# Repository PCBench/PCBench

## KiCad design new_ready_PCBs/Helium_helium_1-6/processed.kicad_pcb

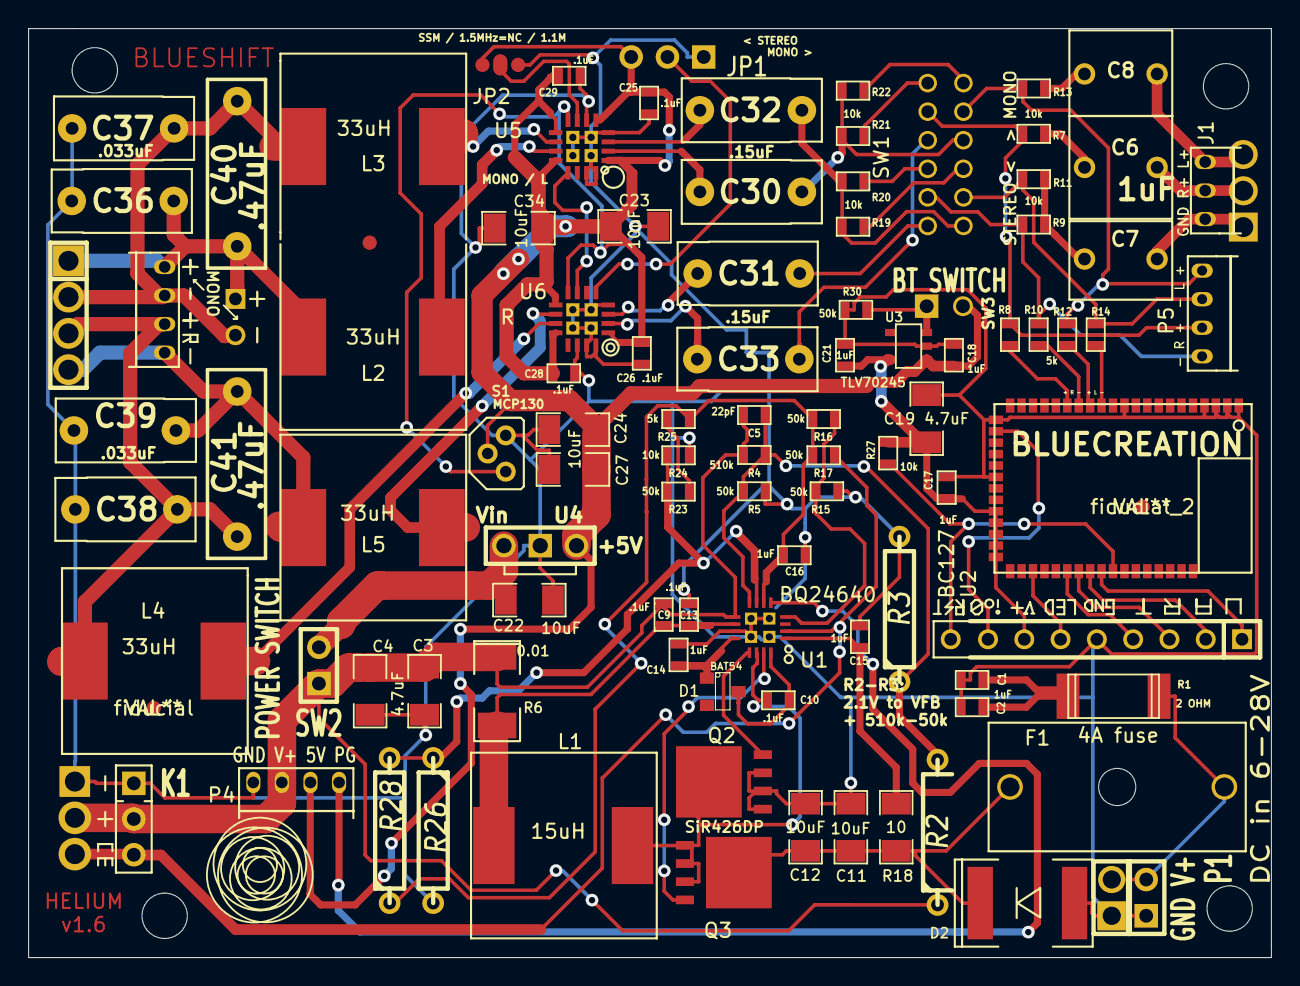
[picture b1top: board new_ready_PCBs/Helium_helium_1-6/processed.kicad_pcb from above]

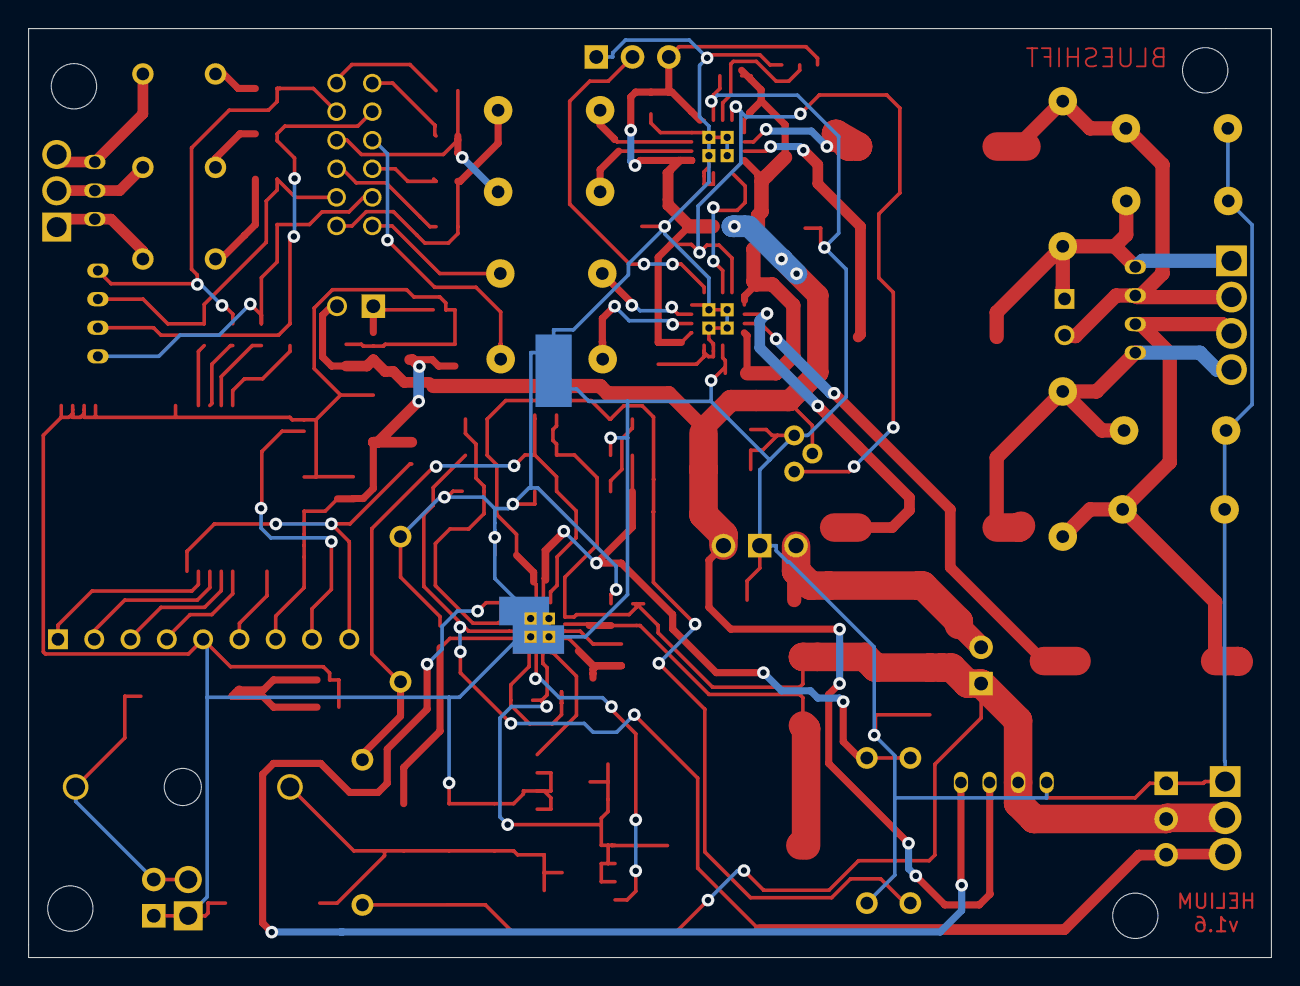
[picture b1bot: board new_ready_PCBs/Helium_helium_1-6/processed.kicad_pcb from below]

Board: 2 copper layers, 87.0 x 65.0 mm, 112 parts (2 on the bottom side), 69 nets.

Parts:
C1, C2, C14, C15, C16, C17, C18, C21: 1uF; SM0603
C3, C4, C19: 4.7uF; SM1206
C5: 22pF; SM0603
C6, C7, C8: 1uF; cnp_7mm_035holes
C9, C10, C13, C25, C26, C28, C29: .1uF; SM0603
C11, C12, C22, C23, C24, C27, C34: 10uF; SM1206
C30, C31, C32, C33: .15uF; cnp_10x4.5mm
C36, C37, C38, C39: .033uF; cnp_10x4.5mm
C40, C41: .47uF; cnp_13x4mm
D1: BAT54; SOT23
D2: 10A diode; SM2010
F1: 4A fuse; fuse
J1: GND R+ L+; h3_2mm
JP1: < STEREO; SIL-3
JP2: SSM / 1.5MHz=NC / 1.1M; jump
K1: TO SUPERCAPS: GND / V+ / CE; SIL-4
L1: 15uH; SRR1280 inductor
L2: 33uH; SRR1280_ind_outline
L3, L4, L5: 33uH; SRR1280 inductor
P1: GND V+; SIL-2
P2: 4xUART/GND/LED/V+/IO; SIL-8-outputs
P3, P5: CONN_4; h4_2mm
P4: GND V+ 5V PG; h4_2mm
Q2, Q3: SiR426DP; PowerPak SO-8 Single
R1: 2 OHM; r_2512
R2: 931k MONO ONLY; R4
R3, R26, R28: DNP; R4
R4: 510k; SM0603
R5, R15, R16, R17, R23, R30: 50k; SM0603
R6: 0.01; SM2010
R7, R9, R11, R13, R19, R20, R21, R22, R24, R27: 10k; SM0603
R8, R10, R12, R14, R25: 5k; SM0603
R18: 10; SM1206
S1: MCP130; TO92PN
SIL-2, SIL-2_2: Val**; SIL-2
SIL-3, SIL-3_2: Val**; SIL-3
SIL-4: Val**; SIL-4
SW1: STEREO < > MONO; 4PDT MMS42R
SW2: POWER SWITCH; SIL-2
SW3: BT SWITCH; SIL-2
U1: BQ24640; BQ24640 QFN16
U2: BC127; bC127
U3: TLV70245; SOT23-5
U4: U4; SIL-3
U5: MONO / L; max9759
U6: R; max9759
XXX1, XXX3: SHORT!
fiducial: VAL**; fiducial
fiducial_2, fiducial_3: VAL**; fiducial
hole: Val**; hole
hole_2, hole_3, hole_4: Val**; hole
xxx2: short; SHORT!

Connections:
CAPGND: C1.2, C2.2, C3.2, C4.2, C11.2, C12.2, C14.2, C17.2, C18.2, C19.2, C21.2, C22.2, C24.2, C27.2, C28.2, C29.2, C34.2, C36.2, C37.1, C38.2, C39.1, D2.1, K1.1, P1.2, P2.5, P4.1, Q2.1, Q2.2, Q2.3, R24.2, R26.2, R30.2, S1.3, SIL-2.2, SIL-3_2.1, U1.11, U2.1, U2.2, U2.3, U2.4, U2.11, U2.22, U2.27, U3.2, U4.2, U5.6, U6.14, XXX1.2, xxx2.1
CAPV+: C3.1, C4.1, C5.1, C9.2, K1.2, P4.2, R2.1, R4.1, R6.1, SIL-3_2.2, SW2.1, U1.9
CE: K1.3, R17.2, SIL-3_2.3, U1.2
GNDA: C13.2, C15.2, C16.2, C23.2, C25.2, C26.2, JP1.1, JP2.3, R3.2, R5.2, R15.2, U5.4, U5.15, U5.16, U6.4, U6.15, U6.16, XXX1.1, xxx2.2
unnamed: JP1.2, U6.5
unnamed: P2.1, U2.43
unnamed: R22.1, SW1.12
unnamed: P5.1, R9.2, R10.1, SW1.2
unnamed: P5.2, R7.2, R8.1, SW1.5
unnamed: R21.1, SW1.6
unnamed: P5.3, R11.2, R14.1, SW1.8
unnamed: R20.1, SW1.3
unnamed: R19.1, SW1.9
unnamed: R10.2, U2.15
unnamed: P2.2, U2.42
unnamed: P2.3, U2.41
unnamed: P2.4, U2.40
unnamed: P2.9, R27.1, U2.44
unnamed: R14.2, U2.13
unnamed: C6.1, J1.2, SIL-3.2
unnamed: R12.2, U2.14
unnamed: R8.2, U2.16
unnamed: P5.4, R12.1, R13.2, SW1.11
unnamed: C30.1, U5.2
unnamed: C32.1, U5.3
unnamed: C31.2, U6.3
unnamed: C33.2, U6.2
unnamed: C5.2, R2.2, R3.1, R4.2, R5.1, U1.8
unnamed: C10.2, D1.2, U1.16
unnamed: C14.1, D1.1, U1.12
unnamed: R15.1, R16.2, U1.4
unnamed: L2.1, U5.11
unnamed: L5.1, U6.10
unnamed: L4.1, U6.11
unnamed: U5.13, U6.7
unnamed: C22.1, SW2.2, U4.3
unnamed: C8.1, J1.3, SIL-3.3
unnamed: R23.1, R25.2
unnamed: R23.2, R24.1, R26.1, R28.2, U1.7
unnamed: C31.1, SW1.1
unnamed: F1.1, P1.1, R1.1, SIL-2.1
unnamed: P4.4, U1.5
unnamed: C7.2, R9.1, R11.1
unnamed: C7.1, J1.1, SIL-3.1
unnamed: C8.2, R13.1
unnamed: L3.1, U5.10
unnamed: C32.2, R19.2, R20.2, SW1.7
unnamed: C30.2, R21.2, R22.2, SW1.10
unnamed: C33.1, SW1.4
unnamed: C6.2, R7.1
unnamed: P2.6, U2.37
unnamed: P2.8, U2.23
unnamed: JP2.2, U5.7
unnamed: C23.1, C25.1, C26.1, JP1.3, JP2.1, S1.1, U5.1, U5.5, U5.8, U6.1, U6.8, XXX3.2
unnamed: C11.1, C12.1, D2.2, F1.2, Q3.5, Q3.6, Q3.7, Q3.8, R18.1
unnamed: C10.1, L1.1, Q2.5, Q2.6, Q2.7, Q2.8, Q3.1, Q3.2, Q3.3, U1.14
unnamed: Q3.4, U1.15
unnamed: C16.1, R16.1, R17.1, R25.1, R28.1, U1.6
unnamed: Q2.4, U1.13
unnamed: C1.1, C2.1, R1.2
unnamed: C15.1, R18.2, U1.1
unnamed: C18.1, C24.1, C27.1, C28.1, C29.1, C34.1, P4.3, S1.2, SW3.2, U3.1, U4.1, U5.9, U5.12, U6.9, U6.12, XXX3.1
unnamed: C36.1, C40.1, L2.2, P3.1, SIL-2_2.1, SIL-4.1
unnamed: C37.2, C40.2, L3.2, P3.2, SIL-2_2.2, SIL-4.2
unnamed: C9.1, C13.1, L1.2, R6.2, U1.10
unnamed: R30.1, SW3.1, U3.3
unnamed: C17.1, C19.1, C21.1, P2.7, R27.2, U2.30, U2.31, U2.32, U2.33, U2.34, U3.5
unnamed: C38.1, C41.1, L4.2, P3.3, SIL-4.3
unnamed: C39.2, C41.2, L5.2, P3.4, SIL-4.4

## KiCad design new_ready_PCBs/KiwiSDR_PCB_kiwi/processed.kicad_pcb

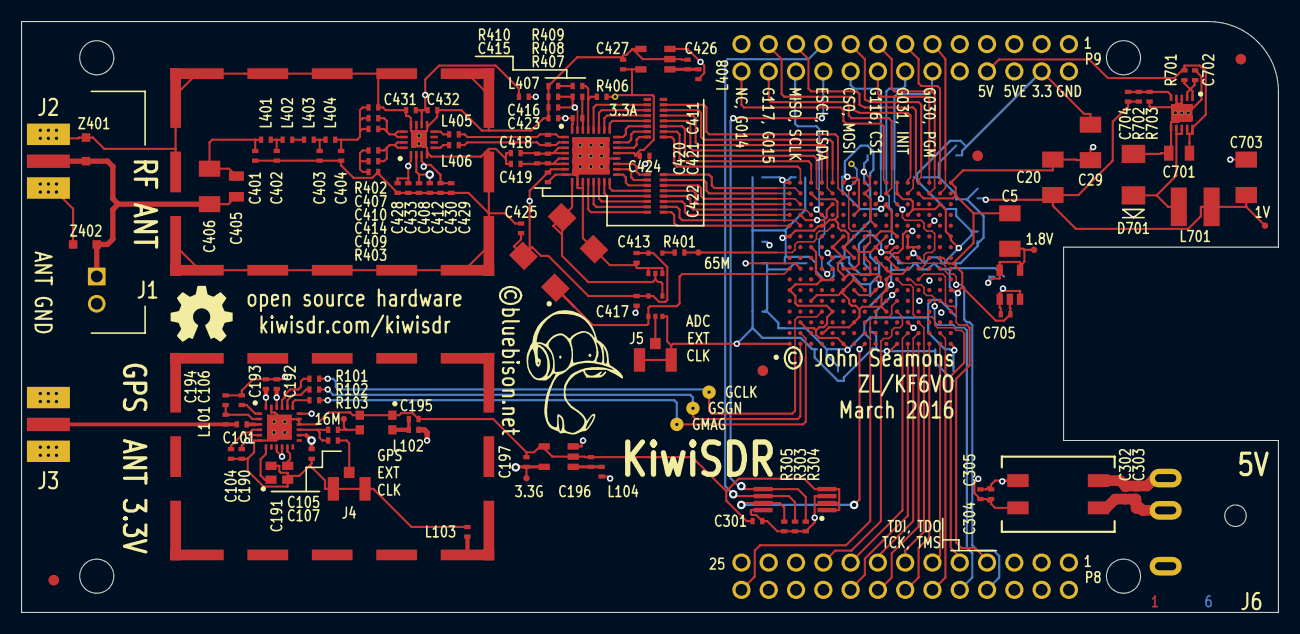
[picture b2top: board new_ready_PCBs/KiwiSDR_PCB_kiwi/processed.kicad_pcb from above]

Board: 6 copper layers, 117.0 x 55.0 mm, 173 parts (0 on the bottom side), 119 nets.

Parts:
C1, C2, C3, C6, C7, C8, C11, C12, C13, C15, C16, C23, C24, C25, C26, C30, C31, C32, C33, C36, C37, C38, C39, C42, C302, C304, C410, C414: 470n; kiwi-SM0402
C5, C20, C29, C703: 100u; kiwi-SM1206
C9, C14, C17, C18, C27, C28, C34, C35, C40, C41, C706: 4.7u; kiwi-SM0402
C101, C104: 22p; kiwi-SM0402
C105, C106, C193, C303, C305, C413, C417, C425: 10n; kiwi-SM0402
C107: DNL 10n; kiwi-SM0402
C190, C191, C192, C195, C301, C421, C422, C423, C424, C429, C431, C433, C702, C704: 100n; kiwi-SM0402
C194, C408, C411, C416: 100p; kiwi-SM0402
C196, C197, C418, C419, C426, C427, C705: 1u; kiwi-SM0402
C401, C404: 56p/100; kiwi-SM0402
C402, C403: 160p/50; kiwi-SM0402
C405: 1n/100; kiwi-SM0805
C406: 470n/100; kiwi-SM1206
C407, C409, C428, C430, C432: 1n; kiwi-SM0402
C412, C415, C420: 2.2u; kiwi-SM0402
C701: 22u; kiwi-SM0805
D701: SR 5A 40V; kiwi-DO214_AA
FID1, FID2: FPGA FIDUCIAL; kiwi-FIDUCIAL
FID3, FID4, FID5, FID6: GLOBAL FIDUCIAL; kiwi-FIDUCIAL
FL101: SAW L1; kiwi-SAW
GFX1: LOGO; kiwi-KIWI_10MM
GFX2: OSHW; kiwi-OSHW_6MM
J1: TB_2; kiwi-TB_2P_2_54MM
J2, J3: SMA; kiwi-SMA_OPL_EM
J4, J5: DNL U.FL; kiwi-U.FL
J6: POWER JACK 2.1MM; kiwi-JACK_2_1MM_TH
L101: 39nH; kiwi-SM0402
L102, L103, L104, L407, L408: FB 600Z; kiwi-SM0402
L401, L404: 330nH; kiwi-SM0402
L402: 270nH; kiwi-SM0402
L403, L405, L406: 150nH; kiwi-SM0402
L701: 1uH 3.7A; kiwi-INDUCTOR_4x4
R101, R102, R103, R401: 100R; kiwi-SM0402
R303, R304, R305: 5K6; kiwi-SM0402
R402: 66R5; kiwi-SM0402
R403: 28R7; kiwi-SM0402
R404, R405: 100R; kiwi-RNET_CAY16_J8
R406, R409, R410, R703: 10K; kiwi-SM0402
R407: DNL; kiwi-SM0402
R408: 0R; kiwi-SM0402
R701: 10R; kiwi-SM0402
R702: 6K65; kiwi-SM0402
T301: CMC 500uH 1A; kiwi-CMC
TP101, TP105, TP401, TP701, TP702: TEST_POINT; kiwi-TP_600
TP102, TP103, TP104: TEST_POINT; kiwi-TP_VIA_1250
TP301, TP402: TEST_POINT; kiwi-TP_VIA_600
U1: Artix-7 A35; kiwi-FTG256
U101: SE4150L; kiwi-QFN24
U104, U404: LP5907 3.3V 250mA; kiwi-SOT23_5
U301: EEPROM 32Kx8; kiwi-TSSOP8
U401: LTC2248; kiwi-QFN32
U402: 66.6666 MHz; kiwi-XO
U403, U406: NC7SZ125; kiwi-SC70_5
U405: LTC6401-20; kiwi-QFN16
U701: LMR10530Y 1.0V 3A; kiwi-WSON10
U702: LP5907 1.8V 250mA; kiwi-SOT23_5
X101: 16.368 MHz; kiwi-TCXO
Z401, Z402: TVS 3.3V; kiwi-SOD323
ZB1: HEADER 13x2; kiwi-BEAGLEBONE_BLACK
ZR101: RF_SHIELD 29x19; kiwi-RF_SHIELD_29x19_16P
ZR102, ZR402: RF_SHIELD_COVER 29x19; kiwi-RF_SHIELD_COVER
ZR401: RF_SHIELD 29x19; kiwi-RF_SHIELD_29x19

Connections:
1.0: C2.1, C3.1, C8.1, C9.1, C14.1, C15.2, C20.1, C42.2, C703.1, C704.1, L701.2, R702.1, TP701.1, U1.E10, U1.F7, U1.F9, U1.F11, U1.G6, U1.H9, U1.J6, U1.K9, U1.L8
1.8: C1.1, C5.1, C7.1, C13.1, C706.1, TP702.1, U1.F8, U1.G8, U1.G10, U1.J10, U1.K11, U1.L10, U702.4, U702.5
3.3: C6.1, C11.1, C12.1, C16.1, C17.1, C18.1, C23.1, C24.1, C25.1, C26.1, C27.1, C28.1, C29.1, C30.1, C31.1, C32.1, C33.1, C34.1, C35.1, C36.1, C37.1, C38.1, C39.1, C40.1, C41.1, C301.2, R303.1, R304.1, R305.1, U1.A6, U1.A16, U1.B3, U1.B13, U1.C10, U1.D7, U1.E4, U1.E7, U1.E14, U1.F1, U1.H15, U1.J12, U1.L6, U1.L15, U1.L16, U1.M3, U1.M9, U1.M10, U1.M11, U1.M13, U1.N10, U1.P7, U1.R4, U1.R14, U1.T1, U1.T11, U301.3, U301.8, ZB1.903, ZB1.904
3.3A: C413.1, C417.1, C422.2, C423.2, C424.1, C425.1, C427.1, L407.1, R406.1, R407.1, TP402.1, U401.7, U401.21, U401.32, U402.4, U403.5, U404.5, U406.5
3.3G: C190.1, C191.1, C192.2, C193.2, C197.1, L102.2, TP105.1, U101.5, U101.9, U101.10, U101.14, U101.18, U101.22, U101.24, U104.5
5EXT: C304.1, C305.1, T301.1, ZB1.905, ZB1.906
5V: C701.1, C705.1, L104.2, L408.2, R701.1, U104.3, U404.3, U701.9, U701.10, U702.1, U702.3, ZB1.907, ZB1.908
/ADC/AD0: R405.15, U401.12
/ADC/AD1: R405.13, U401.13
/ADC/AD2: R405.11, U401.14
/ADC/AD3: R405.9, U401.15
/ADC/AD4: R405.7, U401.16
/ADC/AD5: R405.5, U401.17
/ADC/AD6: R405.3, U401.18
/ADC/AD7: R405.1, U401.19
/ADC/AD8: R404.15, U401.22
/ADC/AD9: R404.13, U401.23
/ADC/AD10: R404.11, U401.24
/ADC/AD11: R404.9, U401.25
/ADC/AD12: R404.7, U401.26
/ADC/AD13: R404.5, U401.27
/ADC/ADOV: R404.3, U401.28
/ADC/AIN+: C411.1, L405.2, U401.1
/ADC/AIN-: C411.2, L406.2, U401.2
/ADC/ANT+: C405.1, C406.1, J1.1, J2.1, Z401.2, Z402.2
/ADC/AXO: U401.9, U402.3, U403.4, U406.2
/ADC/ECLK: J5.1, U403.2
/ADC/IN+: C407.2, C410.2, U405.13, U405.14
/ADC/IN-: C409.2, C414.2, U405.15, U405.16
/ADC/LCLK: R401.1, U406.4
/ADC/LP1: C401.1, C405.2, C406.2, L401.1
/ADC/LP2: C402.1, L401.2, L402.1
/ADC/LP3: L402.2, L403.1
/ADC/LP4: C403.1, L403.2, L404.1
/ADC/MD1: R409.2, R410.1
/ADC/MODE: R406.2, R409.1, U401.29
/ADC/OUT+: L405.1, U405.8
/ADC/OUT-: L406.1, U405.5
/ADC/REFH: C418.2, C420.1, C421.1, U401.3, U401.4
/ADC/REFL: C419.2, C420.2, C421.2, U401.5, U401.6
/ADC/RF+: C404.1, C407.1, C410.1, L404.2, R402.1
/ADC/RF-: C409.1, C414.1, R403.2
/ADC/SENSE: R407.2, R408.2, U401.30
/ADC/VA: C428.2, C429.2, C430.2, C431.1, C432.1, C433.2, L407.2, U405.1, U405.3, U405.10
/ADC/VCM: C408.1, C412.1, C415.1, C416.1, R408.1, U401.31, U405.2
/ADC/VIN: C426.1, L408.1, U404.1
/BeagleBone/5V_NEG: C302.2, C303.2, J6.2, J6.3, T301.3
/BeagleBone/5V_POS: C302.1, C303.1, J6.1, T301.4
/BeagleBone/CS0: U1.N16, ZB1.917
/BeagleBone/CS1: U1.P16, ZB1.916
/BeagleBone/DONE: TP301.1, U1.H10
/BeagleBone/ESCL: R303.2, U301.6, ZB1.919
/BeagleBone/ESDA: R304.2, U301.5, ZB1.920
/BeagleBone/G014: U1.K16, ZB1.926
/BeagleBone/G015: U1.K15, ZB1.924
/BeagleBone/G030: U1.R15, ZB1.911
/BeagleBone/G031: U1.R16, ZB1.913
/BeagleBone/G116: U1.P15, ZB1.915
/BeagleBone/G117: U1.M16, ZB1.923
/BeagleBone/INIT: U1.K10, ZB1.914
/BeagleBone/MISO: U1.M15, ZB1.921
/BeagleBone/MOSI: U1.J14, ZB1.918
/BeagleBone/PGM: U1.L9, ZB1.912
/BeagleBone/TCK: U1.L7, ZB1.809
/BeagleBone/TDI: U1.N7, ZB1.807
/BeagleBone/TDO: U1.N8, ZB1.808
/BeagleBone/TMS: U1.M7, ZB1.810
/GPS/EOSC: C107.2, J4.1
/GPS/GBIAS: C194.2, L101.2, U101.2
/GPS/GPS: C101.1, J3.1, L101.1
/GPS/GPS2: C101.2, U101.3
/GPS/LCLK: R101.1, U101.21
/GPS/LMAG: R103.1, U101.19
/GPS/LNA: C104.1, U101.4
/GPS/LSGN: R102.1, U101.20
/GPS/RING: L103.2, ZR101.1
/GPS/SAW1: FL101.1, U101.7
/GPS/SAW2: FL101.3, U101.11
/GPS/TCXO1: C105.1, C107.1, U101.15
/GPS/TCXO2: C105.2, TP101.1, X101.3
/GPS/TXOP: C195.1, L102.1, X101.4
/GPS/VAGC: C106.2, U101.1
/GPS/VIN: C196.1, L104.1, U104.1
/Power_Supplies/EN: C702.1, R701.2, U701.1, U701.2
/Power_Supplies/FB: C704.2, R702.2, R703.1, U701.5
/Power_Supplies/SW1: D701.1, L701.1, U701.7, U701.8
ACLK: R401.2, TP401.1, U1.E12
AEXT: U1.A8, U402.1, U403.1
D0: R405.16, U1.A12
D1: R405.14, U1.B12
D2: R405.12, U1.A13
D3: R405.10, U1.C13
D4: R405.8, U1.A14
D5: R405.6, U1.B14
D6: R405.4, U1.A15
D7: R405.2, U1.B15
D8: R404.16, U1.B16
D9: R404.14, U1.C16
D10: R404.12, U1.D15
D11: R404.10, U1.D16
D12: R404.8, U1.E15
D13: R404.6, U1.E16
EWP: R305.2, U1.H1, U301.7
G022: U1.L4, ZB1.819
G023: U1.N3, ZB1.813
G026: U1.P1, ZB1.814
G027: U1.M2, ZB1.817
G112: U1.R2, ZB1.812
G113: U1.R1, ZB1.811
G114: U1.N1, ZB1.816
G115: U1.N2, ZB1.815
G129: U1.L5, ZB1.826
G201: U1.M1, ZB1.818
GCLK: R101.2, TP102.1, U1.D4
GMAG: R103.2, TP104.1, U1.B2
GND: C1.2, C2.2, C3.2, C5.2, C6.2, C7.2, C8.2, C9.2, C11.2, C12.2, C13.2, C14.2, C15.1, C16.2, C17.2, C18.2, C20.2, C23.2, C24.2, C25.2, C26.2, C27.2, C28.2, C29.2, C30.2, C31.2, C32.2, C33.2, C34.2, C35.2, C36.2, C37.2, C38.2, C39.2, C40.2, C41.2, C42.1, C104.2, C106.1, C190.2, C191.2, C192.1, C193.1, C194.1, C195.2, C196.2, C197.2, C301.1, C304.2, C305.2, C401.2, C402.2, C403.2, C404.2, C408.2, C412.2, C413.2, C415.2, C416.2, C417.2, C418.1, C419.1, C422.1, C423.1, C424.2, C425.2, C426.2, C427.2, C428.1, C429.1, C430.1, C431.2, C432.2, C433.1, C701.2, C702.2, C703.2, C705.2, C706.2, D701.2, FL101.2, FL101.4, J1.2, J2.2, J2.3, J3.2, J3.3, J4.2, J4.3, J5.2, J5.3, L103.1, R402.2, R403.1, R410.2, R703.2, T301.2, U1.A1, U1.A11, U1.B8, U1.C5, U1.C15, U1.D2, U1.D12, U1.E9, U1.F6, U1.F10, U1.F16, U1.G3, U1.G7, U1.G9, U1.G13, U1.H6, U1.J9, U1.J11, U1.K4, U1.K6, U1.K7, U1.K8, U1.K14, U1.L1, U1.L11, U1.M8, U1.N5, U1.N15, U1.P12, U1.R9, U1.T6, U1.T16, U101.6, U101.16, U101.17, U101.23, U101.PAD, U104.2, U104.4, U301.1, U301.2, U301.4, U401.8, U401.10, U401.11, U401.20, U401.PAD, U402.2, U403.3, U404.2, U404.4, U405.4, U405.9, U405.11, U405.12, U405.PAD, U406.1, U406.3, U701.3, U701.4, U701.6, U701.PAD, U702.2, X101.1, X101.2, Z401.1, Z402.1, ZB1.901, ZB1.902, ZR401.0
GSGN: R102.2, TP103.1, U1.B1
OVFL: R404.4, U1.F15
SCLK: U1.D13, U1.E8, ZB1.922

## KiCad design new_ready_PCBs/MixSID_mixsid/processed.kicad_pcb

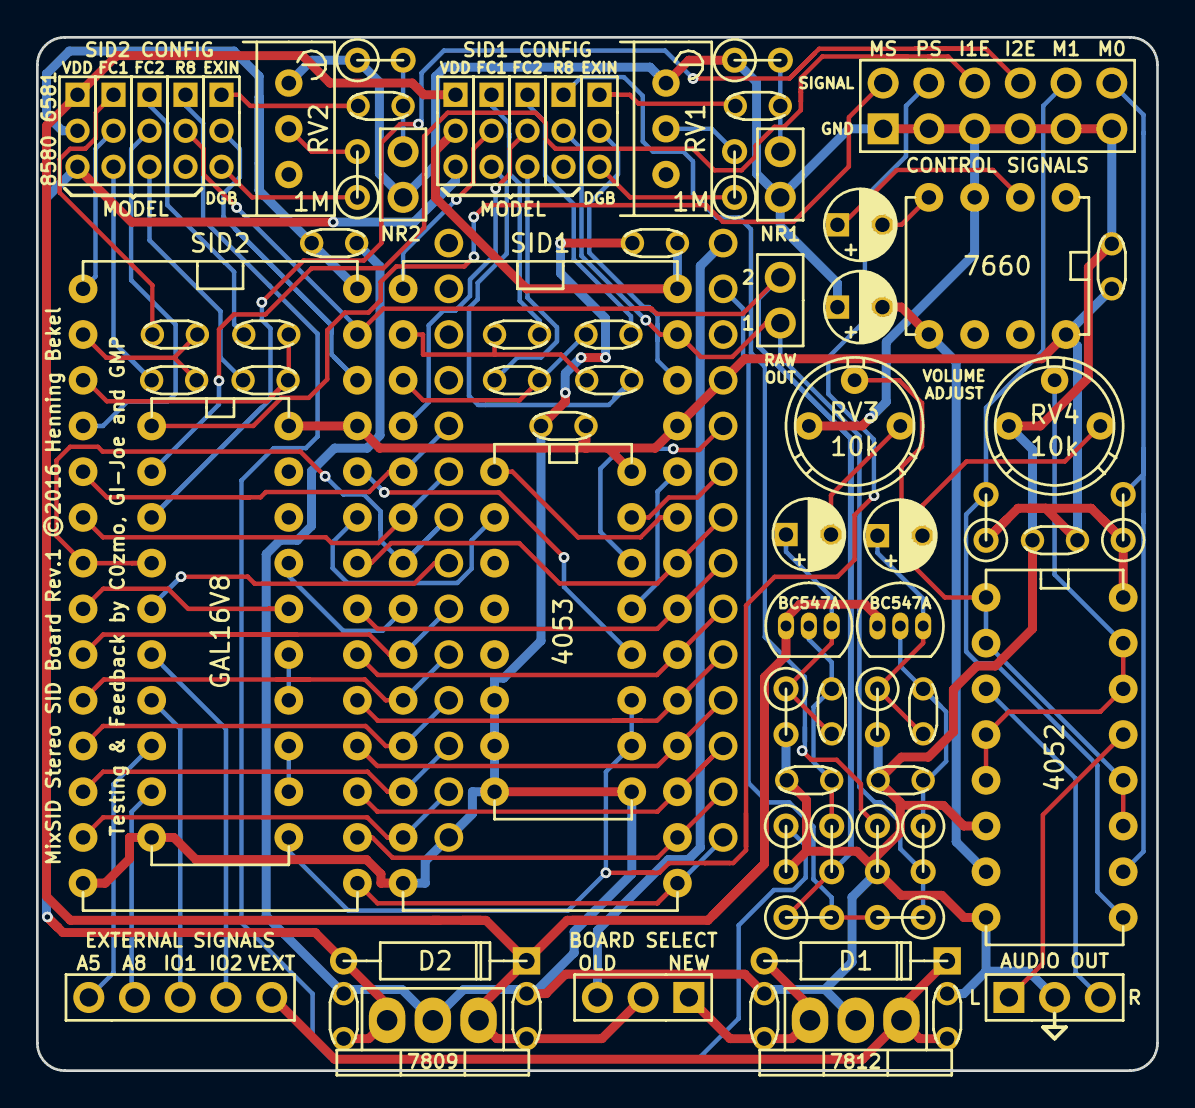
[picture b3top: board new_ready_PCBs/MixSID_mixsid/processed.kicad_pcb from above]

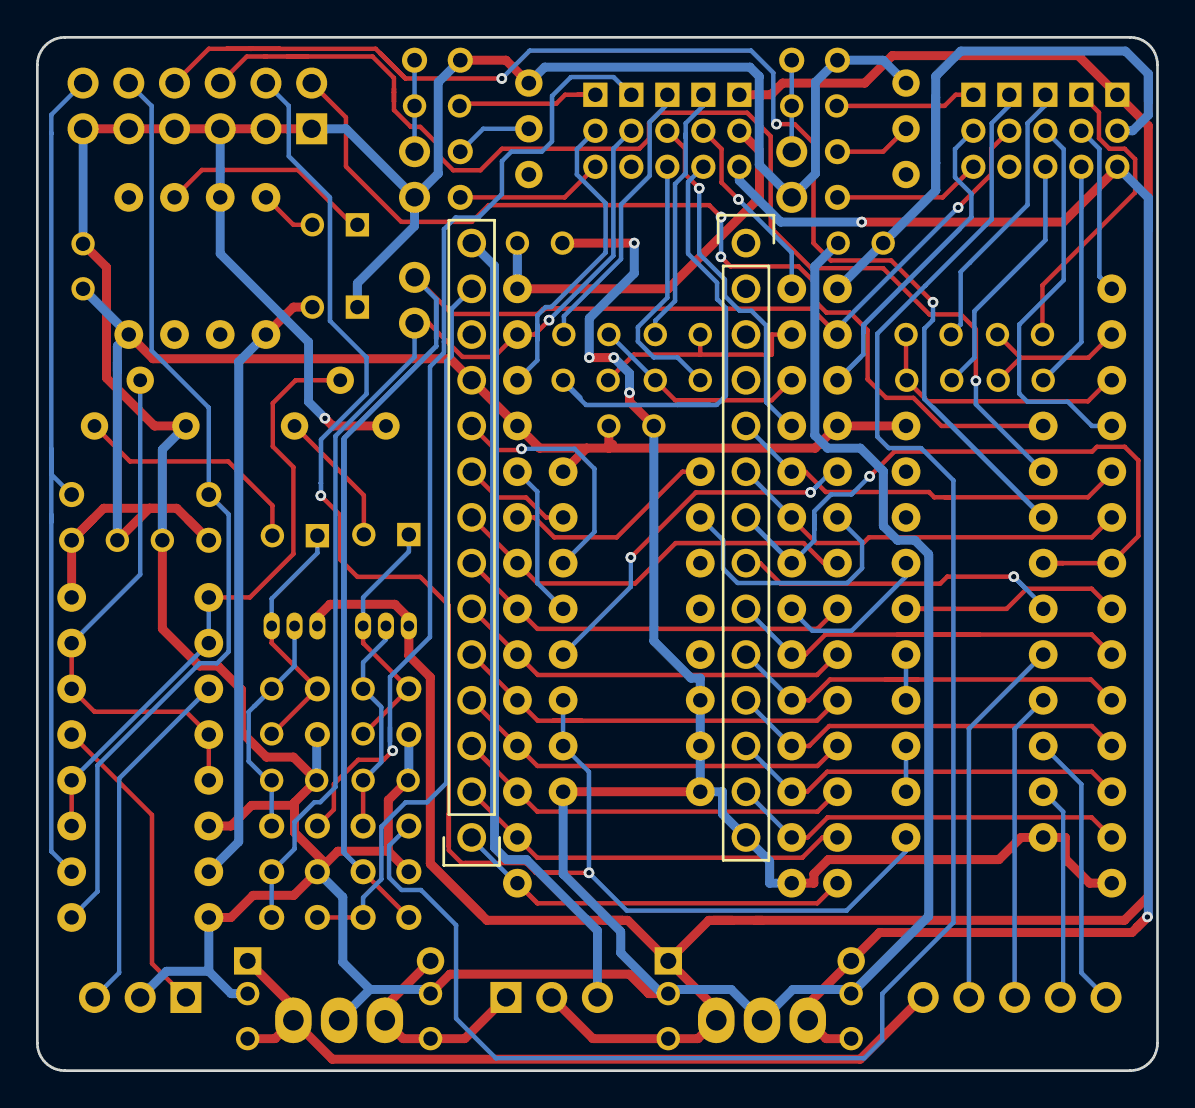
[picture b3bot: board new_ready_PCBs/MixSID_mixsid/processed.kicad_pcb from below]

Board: 2 copper layers, 62.2 x 57.4 mm, 76 parts (2 on the bottom side), 90 nets.

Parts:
C1, C3, C5, C7, C9, C11, C16, C21: 470p; C_Disc_D3_P2.5
C2, C4, C10, C12: 22n; C_Disc_D3_P2.5
C6, C8, C13, C14, C23, C24, C25, C26, C27: 100n; C_Disc_D3_P2.5
C15, C20: 1n; C_Disc_D3_P2.5
C17, C18: 10u; C_Radial_D5_L6_P2.5
C19, C22: 10uF; C_Radial_D5_L6_P2.5
D1, D2: 1N4002; DO-41
JP1: SUPPLY2; Pin_Header_Straight_1x03_Pitch2.00mm_Jumper_1-2
JP2: S2CAP2; Pin_Header_Straight_1x03_Pitch2.00mm_Jumper_1-2
JP3: S2CAP1; Pin_Header_Straight_1x03_Pitch2.00mm
JP4: BOARD; Pin_Header_Straight_1x03
JP5: SUPPLY1; Pin_Header_Straight_1x03_Pitch2.00mm_Jumper_2-3
JP6: S1CAP2; Pin_Header_Straight_1x03_Pitch2.00mm_Jumper_2-3
JP7: S1CAP1; Pin_Header_Straight_1x03_Pitch2.00mm_Jumper_2-3
JP8: INPUT2; Pin_Header_Straight_1x03_Pitch2.00mm_Jumper_1-2
JP9: NR1; Pin_Header_Straight_1x02
JP10: NR2; Pin_Header_Straight_1x02
JP11: INPUT1; Pin_Header_Straight_1x03_Pitch2.00mm_Jumper_2-3
JP12: J2R8; Pin_Header_Straight_1x03_Pitch2.00mm_Jumper_1-2
JP13: J1R8; Pin_Header_Straight_1x03_Pitch2.00mm_Jumper_2-3
P1: INPUT; Pin_Header_Straight_1x05
P2: CONTROL; Pin_Header_Straight_2x06
P3: RAW; Pin_Header_Straight_1x02
P4: SOCKET LEFT; Pin_Header_Straight_1x14
P5: OUTPUT; Pin_Header_Straight_1x03
P6: SOCKET RIGHT; Pin_Header_Straight_1x14
Q1, Q2: BC547; TO-92_Inline_Narrow_Oval
R1, R10: 220k; R1
R2, R9: 100k; R1
R3, R5, R6, R12, R13, R14: 1k; R1
R4, R11: 10k; R1
R7, R8: 4k7; R1
RV1, RV2: 1M; Potentiometer_Bourns_3296W_3-8Zoll_Inline_ScrewUp
RV3, RV4: 10k; Potentiometer_Bourns_3339P_Angular_ScrewUp
U1: GAL16V8; DIP-20_W7.62mm
U2: SID2; DIP-28_W15.24mm
U3: 7812; TO-220
U4: 7809; TO-220
U5: SID1; DIP-28_W15.24mm
U6: 4052; DIP-16_W7.62mm
U7: 4053; DIP-16_W7.62mm
U8: 7660; DIP-8_W7.62mm

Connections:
/+9V: C8.1, D2.2, JP1.3, JP5.3, U4.3
/+12V: C7.1, D2.1, JP1.1, JP4.2, JP5.1, Q1.1, Q2.1, U4.1
/A0: P4.9, U2.9, U5.9
/A1: P4.10, U2.10, U5.10
/A2: P4.11, U2.11, U5.11
/A3: P4.12, U2.12, U5.12
/A4: P4.13, U2.13, U5.13
/A5: P1.1, U1.8
/A8: P1.2, U1.9
/CLK: P4.6, U2.6, U5.6
/D0: P6.1, U2.15, U5.15
/D1: P6.2, U2.16, U5.16
/D2: P6.3, U2.17, U5.17
/D3: P6.4, U2.18, U5.18
/D4: P6.5, U2.19, U5.19
/D5: P6.6, U2.20, U5.20
/D6: P6.7, U2.21, U5.21
/D7: P6.8, U2.22, U5.22
/LEFT: RV3.2, U6.1, U6.2, U6.11, U6.12
/LEFT_OUT: P5.1, U6.13
/M0: P2.12, R7.2, U6.10
/M1: P2.10, R8.2, U6.9
/MONO_OUT: P6.13, R13.2, R14.2
/MS: P2.2, U1.1
/POTX: P6.10, U7.14
/POTX1: U5.24, U7.13
/POTX2: U2.24, U7.12
/POTY: P6.9, U7.15
/POTY1: U5.23, U7.1
/POTY2: U2.23, U7.2
/PS: P2.4, U1.11, U7.10, U7.11
/PWR: C6.1, D1.2, JP4.1, U3.3
/PWR1: C27.1, JP5.2, U5.28
/PWR2: C26.1, JP1.2, U2.28
/RIGHT: RV4.2, U6.4, U6.5, U6.14, U6.15
/RIGHT_OUT: P5.3, U6.3
/RW: P4.7, U1.4, U2.7, U5.7
/S1IN: JP11.2, U5.26
/S1OUT: JP13.2, P3.2, R11.2, R14.1, U5.27
/S2IN: JP8.2, U2.26
/S2OUT: JP12.2, P3.1, R4.2, R13.1, U2.27
/VEE: C18.2, U6.7, U8.5
/VEXT: C5.1, D1.1, P1.5, U3.1
/~CS: P4.8, U1.5
/~CS1: U1.17, U5.8
/~CS2: U1.16, U2.8
/~IO1: P1.3, U1.7
/~IO1EN: P2.6, U1.2
/~IO2: P1.4, U1.6
/~IO2EN: P2.8, U1.3
/~RES: P4.5, U2.5, U5.5
GND: C5.2, C6.2, C7.2, C8.2, C15.2, C18.1, C20.2, C23.2, C24.2, C25.2, C26.2, C27.2, JP9.2, JP10.2, P2.1, P2.3, P2.5, P2.7, P2.9, P2.11, P4.14, P5.2, R2.1, R3.2, R5.2, R6.2, R9.1, R12.2, RV1.1, RV2.1, RV3.1, RV4.1, U1.10, U2.14, U3.2, U4.2, U5.14, U6.6, U6.8, U7.6, U7.7, U7.8, U7.9, U8.3
unnamed: C1.1, C2.2, U2.3
unnamed: C1.2, JP2.1
unnamed: C2.1, JP2.3
unnamed: C3.1, C4.2, U2.2
unnamed: C3.2, JP3.1
unnamed: C4.1, JP3.3
unnamed: C9.2, JP6.1
unnamed: C10.1, JP6.3
unnamed: C9.1, C10.2, U5.3
unnamed: C11.1, C12.2, U5.2
unnamed: C11.2, JP7.1
unnamed: C12.1, JP7.3
unnamed: C13.1, JP10.1, R9.2
unnamed: C13.2, JP8.1
unnamed: C14.1, JP9.1, R2.2
unnamed: C14.2, JP11.1
unnamed: C15.1, C16.1, Q1.2, R4.1
unnamed: C16.2, C19.1, Q1.3, R5.1
unnamed: C17.1, U8.2
unnamed: C17.2, U8.4
unnamed: C19.2, RV3.3
unnamed: C20.1, C21.1, Q2.2, R11.1
unnamed: C21.2, C22.1, Q2.3, R12.1
unnamed: C22.2, RV4.3
unnamed: JP2.2, U2.4
unnamed: JP3.2, U2.1
unnamed: JP6.2, U5.4
unnamed: JP7.2, U5.1
unnamed: JP8.3, R1.1
unnamed: JP11.3, R10.1
unnamed: JP12.1, R3.1
unnamed: JP13.1, R6.1
unnamed: R1.2, RV2.2
unnamed: R10.2, RV1.2
unnamed: U1.12, U1.13
unnamed: U1.14, U1.15
VCC: C23.1, C24.1, C25.1, P6.11, R7.1, R8.1, U1.20, U2.25, U5.25, U6.16, U7.16, U8.8
VDD: JP4.3, P6.14

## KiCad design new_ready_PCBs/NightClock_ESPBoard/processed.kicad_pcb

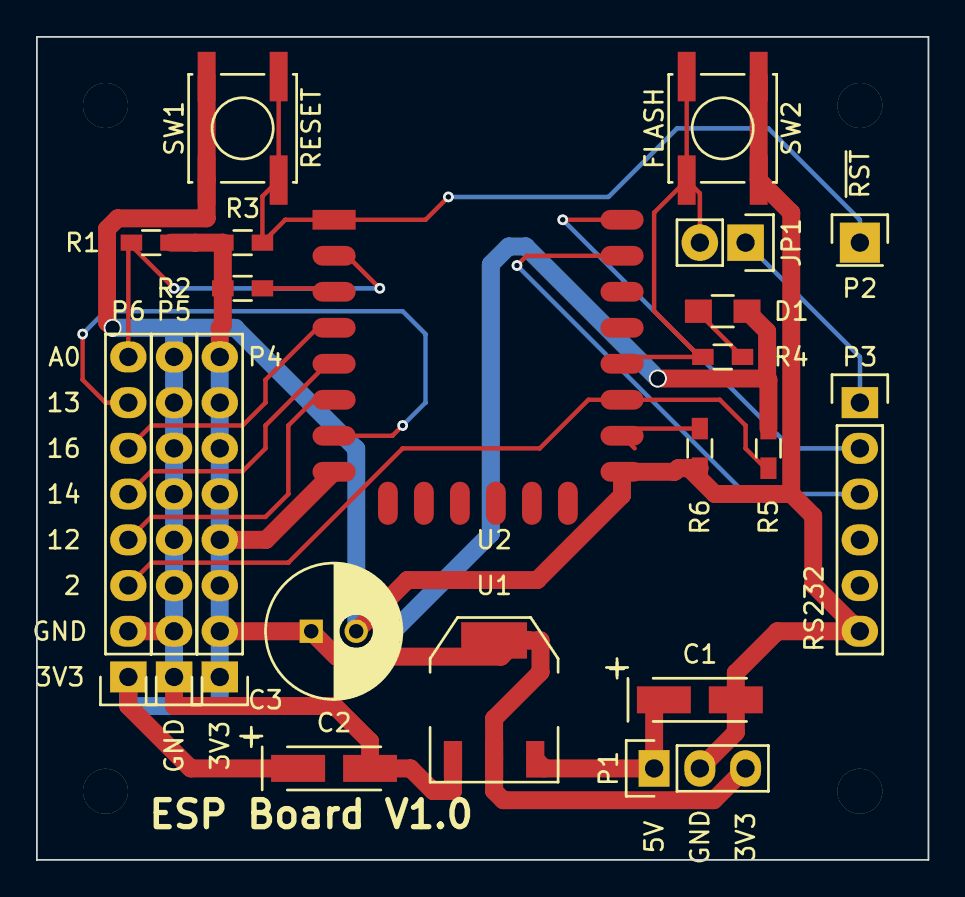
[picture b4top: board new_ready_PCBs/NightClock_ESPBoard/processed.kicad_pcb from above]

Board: 2 copper layers, 49.5 x 45.7 mm, 21 parts (0 on the bottom side), 17 nets.

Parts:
C1, C2: 10u; TantalC_SizeA_EIA-3216_HandSoldering
C3: 1000u; C_Radial_D7.5_L11.2_P2.5
D1: LED; R_0805_HandSoldering
JP1: AUTO_FLASH; Pin_Header_Straight_1x02
P1: PWR; Pin_Header_Straight_1x03
P2: EXT_RESET; Pin_Header_Straight_1x01
P3: RS232; Pin_Header_Straight_1x06
P4: 3.3V; Pin_Header_Straight_1x08
P5: Gnd; Pin_Header_Straight_1x08
P6: GPIO; Pin_Header_Straight_1x08
R1: 470k; R_0603_HandSoldering
R2, R3, R5, R6: 10k; R_0603_HandSoldering
R4: 330R; R_0603_HandSoldering
SW1: RESET; SW_SPST_EVPBF
SW2: FLASH; SW_SPST_EVPBF
U1: LM1117-3.3; SOT-223
U2: ESP-12E

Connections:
+3V3: C2.1, C3.1, D1.2, P1.3, P4.1, P4.2, P4.3, P4.4, P4.5, P4.6, P4.7, P4.8, P6.1, R1.1, R2.1, R3.1, R5.1, U1.2, U1.4, U2.8
+5V: C1.1, P1.1, U1.3
/ESP_ADC: P6.8, R1.2, U2.2
/ESP_CH_PD: R2.2, U2.3
/ESP_GPIO0: JP1.2, R4.2, SW2.2, U2.18
/ESP_GPIO2: P6.3, R5.2, U2.17
/ESP_GPIO12: P6.4, U2.6
/ESP_GPIO13: P6.7, U2.7
/ESP_GPIO14: P6.5, U2.5
/ESP_GPIO15: R6.1, U2.16
/ESP_GPIO16: P6.6, U2.4
/ESP_RESET: P2.1, R3.2, SW1.2, U2.1
/ESP_RX_IN: P3.3, U2.21
/ESP_TX_OUT: P3.2, U2.22
/SERIAL_DTR: JP1.1, P3.1
GNDPWR: C1.2, C2.2, C3.2, P1.2, P3.6, P5.1, P5.2, P5.3, P5.4, P5.5, P5.6, P5.7, P5.8, P6.2, R6.2, SW1.1, SW2.1, U1.1, U2.15
unnamed: D1.1, R4.1

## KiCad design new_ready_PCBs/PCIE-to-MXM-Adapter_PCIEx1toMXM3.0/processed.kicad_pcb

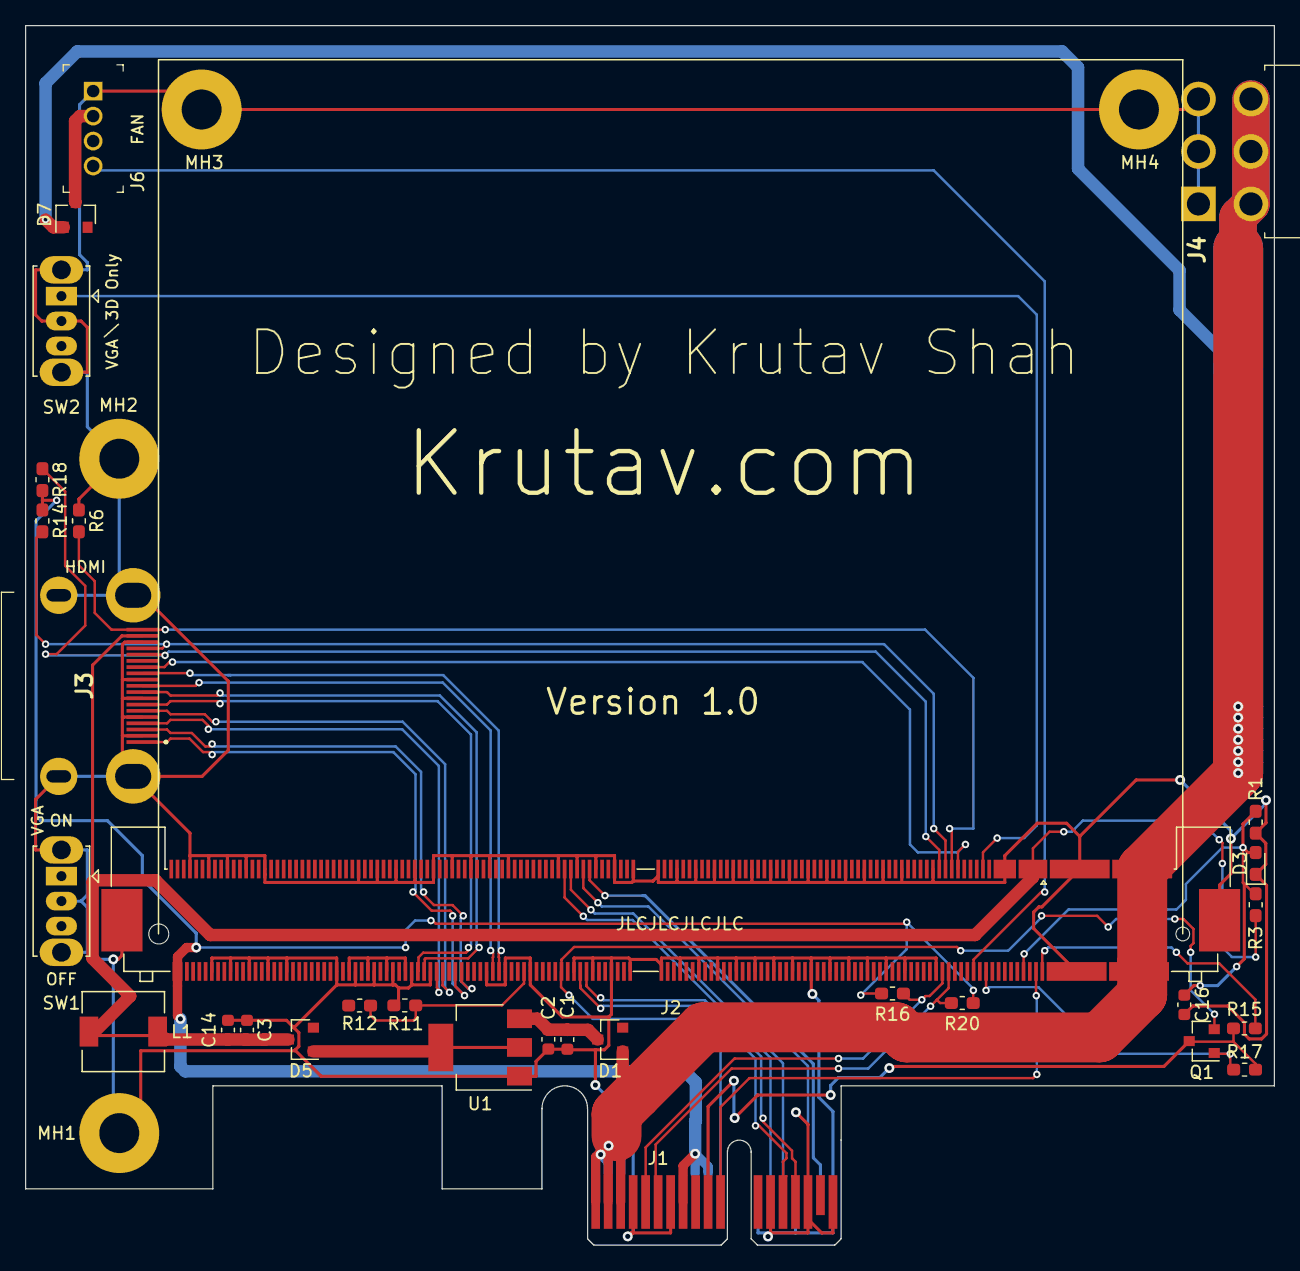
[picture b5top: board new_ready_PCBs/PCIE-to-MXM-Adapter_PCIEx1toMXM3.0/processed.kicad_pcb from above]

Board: 2 copper layers, 100.0 x 97.7 mm, 34 parts (0 on the bottom side), 37 nets.

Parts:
C1, C2, C3, C14, C16: C_0603_1608Metric
D1, D5, D7: PMEG4010ET; D_SOT-23_ANK
D3: LED_0603_1608Metric_Pad1.05x0.95mm_HandSolder
J1: Bus_PCI_Express_x1; BUS_PCIexpress_x1
J2: MXM3.0; JAE_MM70-314-310B1
J3: 208658-1081; 2086581081
J4: 45558-0003; 455580003
J6: PinHeader_1x4_P2mm_Drill1mm
L1: L_6.3x6.3_H3
MH1, MH2, MH3, MH4: MountingHole_3.2mm_M3_Pad
Q1: BC848; SOT-23
R1, R3, R6, R11, R12, R14, R15, R16, R17, R18, R20: R_0603_1608Metric_Pad1.05x0.95mm_HandSolder
SW1, SW2: SW_Slide_1P2T_CK_OS102011MS2Q
U1: AMS1117-5.0; SOT-223-3_TabPin2

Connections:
+3.3VA: J1.B10, Q1.3, R15.2, R17.2
+3V3: J1.A9, J1.A10, J1.B8, J2.278, J2.280, R14.1, R16.1, R18.2, R20.2
+5V: C3.2, C14.2, J2.1, J2.3, J2.5, J2.7, J2.9, J3.18, L1.1, L1.2, R3.1
+12V: D1.2, D7.2, J1.A2, J1.A3, J1.B1, J1.B2, J1.B3, J2.E1, J2.E2, J4.1, J4.2, J4.3
/CK_N: J2.176, J3.12
/CK_P: J2.178, J3.10
/D0_N: J2.200, J3.9
/D0_P: J2.202, J3.7
/D1_N: J2.194, J3.6
/D1_P: J2.196, J3.4
/D2_N: J2.188, J3.3
/D2_P: J2.190, J3.1
/DP_D_L3#: J2.206, J2.212, J2.218, J2.224
/PER0_N: J1.A17, J2.147
/PER0_P: J1.A16, J2.149
/PERST: J1.A11, J2.156, Q1.2
/PET0_N: J1.B15, J2.148
/PET0_P: J1.B14, J2.150
/PRSNT_R#: J2.2, R15.1
/REFCLK_N: J1.A14, J2.153
/REFCLK_P: J1.A13, J2.155
/SMCLK: J1.B5, J2.34, R16.2
/SMDAT: J1.B6, J2.32, R20.1
/TH_OVERT#: J2.20, Q1.1, R17.1
/TMDS_HPD: J2.31, J3.19, R6.2
/TMDS_SCL: J2.35, J3.15, R18.1
/TMDS_SDA: J2.33, J3.16, R14.2
/VGA_DISABLE#: J2.21, SW2.1
/WAKE: J1.B11, J2.4
CEC: J2.29, J3.13
Enable: C16.1, D3.2, J2.8, R1.2, R3.2
GND: C1.2, C2.2, C3.1, C14.1, C16.2, D3.1, J1.A4, J1.A12, J1.A15, J1.A18, J1.B4, J1.B7, J1.B13, J1.B16, J1.B18, J2.11, J2.13, J2.15, J2.17, J2.36, J2.37, J2.46, J2.47, J2.52, J2.53, J2.58, J2.59, J2.64, J2.65, J2.70, J2.71, J2.76, J2.77, J2.82, J2.83, J2.88, J2.89, J2.94, J2.95, J2.100, J2.101, J2.106, J2.107, J2.112, J2.113, J2.118, J2.119, J2.124, J2.125, J2.133, J2.134, J2.139, J2.140, J2.145, J2.146, J2.151, J2.152, J2.157, J2.166, J2.173, J2.174, J2.179, J2.180, J2.185, J2.191, J2.197, J2.198, J2.203, J2.204, J2.209, J2.210, J2.215, J2.216, J2.221, J2.222, J2.228, J2.244, J2.250, J2.251, J2.256, J2.257, J2.262, J2.263, J2.268, J2.269, J2.275, J2.E3, J2.E4, J2.MP, J3.2, J3.5, J3.8, J3.11, J3.17, J3.MH1, J3.MH2, J3.MH3, J3.MH4, J4.4, J4.5, J4.6, J6.1, MH1.1, MH2.1, MH3.1, MH4.1, R1.1, R6.1, R11.1, SW1.2, SW2.2, U1.1
unnamed: C1.1, C2.1, D1.1, U1.3
unnamed: D5.2, U1.2
unnamed: D7.1, J6.2
unnamed: J2.168, R11.2, R12.1
TH_PWM: J2.24, J6.4

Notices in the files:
new_ready_PCBs/KiwiSDR_PCB_kiwi/processed.kicad_pcb:
© John Seamons
©bluebison.net
new_ready_PCBs/MixSID_mixsid/processed.kicad_pcb:
MixSID Stereo SID Board Rev.1 ©2016 Henning Bekel
new_ready_PCBs/PoEPi-hardware_pizero-poe/processed.kicad_pcb:
License: CERN OHL V1.2
CERN OHL V1.2
